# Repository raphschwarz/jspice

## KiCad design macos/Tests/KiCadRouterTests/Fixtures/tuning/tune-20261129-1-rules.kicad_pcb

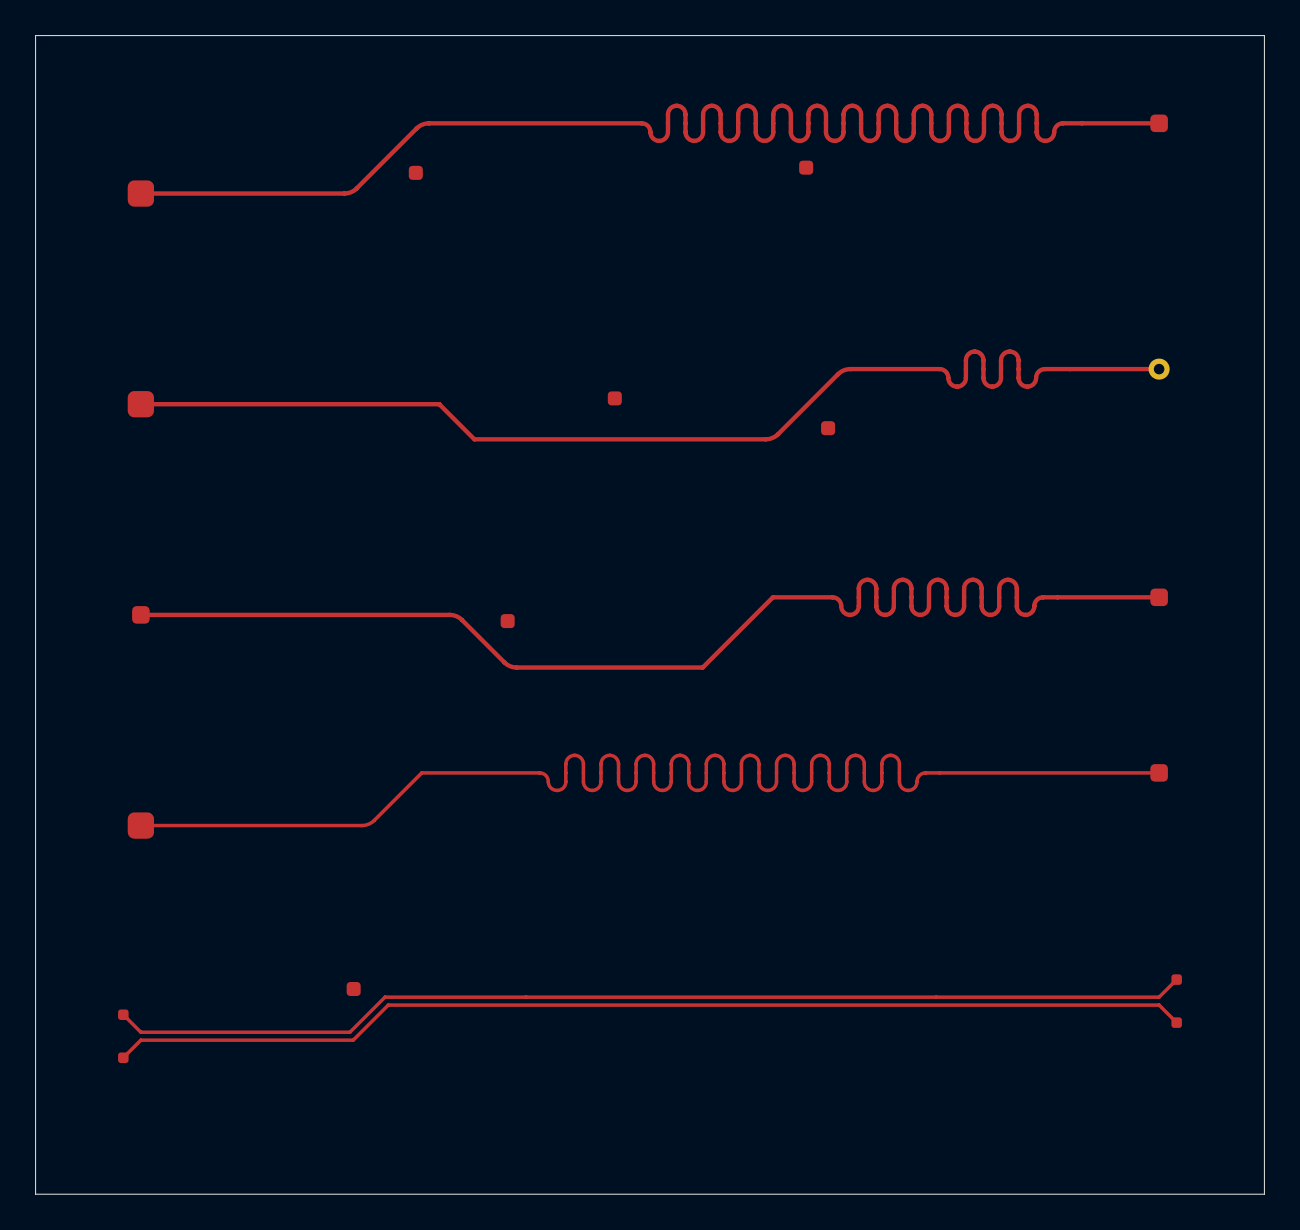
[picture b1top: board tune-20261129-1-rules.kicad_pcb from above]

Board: 2 copper layers, 70.0 x 66.0 mm, 18 parts (0 on the bottom side), 6 nets.

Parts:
P1, P5, P14, P18, P22, P26, P37, P41, P45, P49, P60, P64, P68, P76, P80, P84, P88, P102: Pad

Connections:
D5_N: P84.1, P88.1
D5_P: P76.1, P80.1
S1: P1.1, P5.1
S2: P22.1, P26.1
S3: P45.1, P49.1
S4: P64.1, P68.1
